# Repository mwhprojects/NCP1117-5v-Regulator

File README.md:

# NCP1117 5v Regulator Board
Eagle board and schematic files for a 5v voltage regulator board using NCP1117.

## License Information
<br />This work is licensed under a <a rel="license" href="http://creativecommons.org/licenses/by-sa/4.0/">Creative Commons Attribution-ShareAlike 4.0 International License</a>.

Distributed as-is; no warranty is given.

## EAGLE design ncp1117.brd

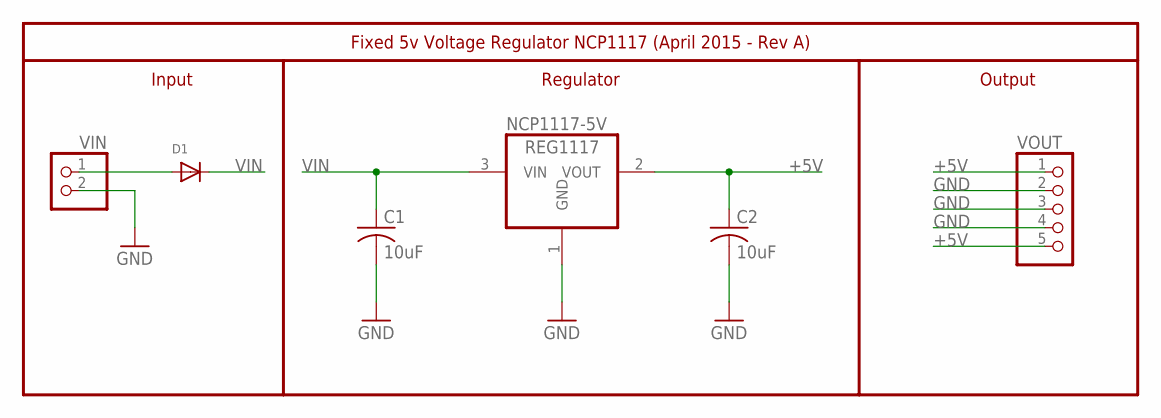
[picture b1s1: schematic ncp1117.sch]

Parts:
C1, C2: 10uF; C0805
D1: DIODESMA; SMADIODE
NCP1117-5V: REG1117; SOT223
VIN: PINHD-1X2; 1X02
VOUT: PINHD-1X5; 1X05

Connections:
+5V: C2.1, NCP1117-5V.2 (VOUT), VOUT.1, VOUT.5
GND: C1.2, C2.2, NCP1117-5V.1 (GND), VIN.2, VOUT.2, VOUT.3, VOUT.4
unnamed: D1.A, VIN.1
VIN: C1.1, D1.C, NCP1117-5V.3 (VIN)

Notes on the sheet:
Fixed 5v Voltage Regulator NCP1117 (April 2015 - Rev A)
Input
Regulator
Output

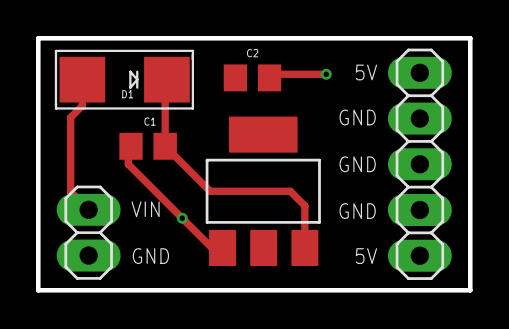
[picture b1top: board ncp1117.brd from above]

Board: 2 copper layers, 24.0 x 14.0 mm, 6 parts (0 on the bottom side), 4 nets.

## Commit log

2015-05-09 :neckbeard: Added .gitattributes & .gitignore files
2015-05-09 Initial Release
    Have at it!

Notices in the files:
parts and their libraries:
SparkFun-Aesthetics: Licensing: Creative Commons ShareAlike 4.0 International - https://creativecommons.org/licenses/by-sa/4.0
